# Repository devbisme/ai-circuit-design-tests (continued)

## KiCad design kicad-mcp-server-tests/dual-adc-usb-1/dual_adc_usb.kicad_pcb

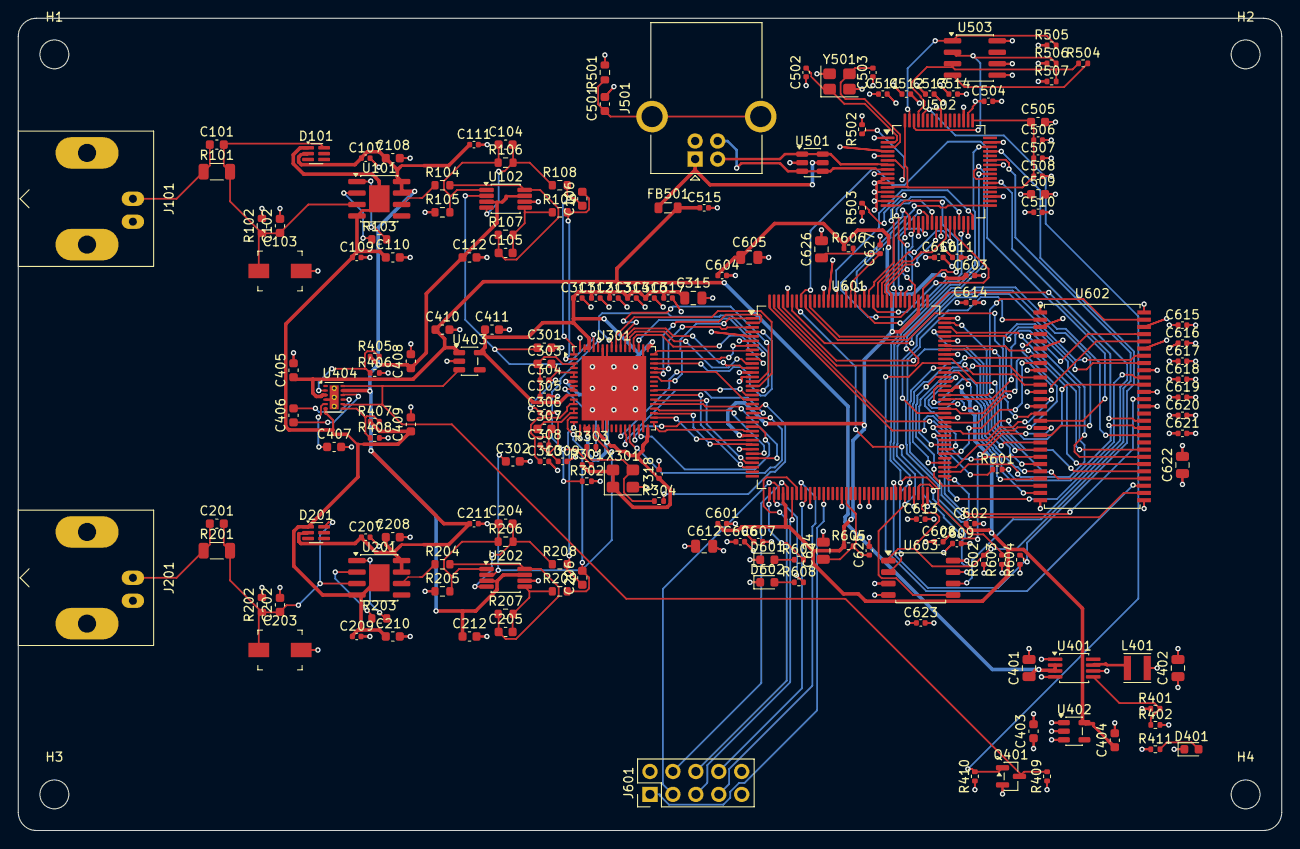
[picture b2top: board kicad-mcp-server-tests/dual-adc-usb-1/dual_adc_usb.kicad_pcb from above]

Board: 4 copper layers, 140.0 x 90.0 mm, 174 parts (0 on the bottom side), 161 nets.

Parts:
C101, C201: 2.2pF C0G; C_0603_1608Metric
C102, C202: 27pF C0G; C_0603_1608Metric
C103, C203: 4.5-20pF; C_Trimmer_Murata_TZB4-A
C104, C105, C204, C205: 22pF C0G; C_0603_1608Metric
C106, C206: 220pF C0G; C_0603_1608Metric
C107, C109, C111, C207, C209, C211, C304, C305, C306, C308, C309, C310, C311, C312, C313, C314, C316, C317, C318, C504, C506, C507, C508, C510, C511, C512, C513, C514, C515, C601, C602, C603, C604, C606, C607, C608, C609, C610, C611, C613, C614, C615, C616, C617, C618, C619, C620, C621, C623, C625, C627: 100nF; C_0402_1005Metric
C108, C110, C112, C208, C210, C212, C403, C404, C406, C410, C411: 1uF; C_0603_1608Metric
C301, C302, C303, C307, C405, C408, C409: 2.2uF; C_0603_1608Metric
C315, C605, C612, C622, C624, C626: 10uF; C_0805_2012Metric
C401: 4.7uF; C_0805_2012Metric
C402: 22uF; C_0805_2012Metric
C407, C505, C509: 4.7uF; C_0603_1608Metric
C501: 4.7nF; C_0603_1608Metric
C502, C503: 18pF; C_0402_1005Metric
D101, D201: BAV199DW; SOT-363_SC-70-6
D401, D601: GREEN; LED_0603_1608Metric
D602: RED; LED_0603_1608Metric
FB501: 600R@100MHz; L_0805_2012Metric
H1, H2, H3, H4: MountingHole_3.2mm_M3
J101, J201: BNC; BNC_Amphenol_B6252HB-NPP3G-50_Horizontal
J501: USB_B; USB_B_OST_USB-B1HSxx_Horizontal
J601: EXP; PinHeader_2x05_P2.54mm_Vertical
L401: 2.2uH; L_Taiyo-Yuden_NR-30xx
Q401: 2N7002; SOT-23
R101, R201: 953k 0.1%; R_1206_3216Metric
R102, R202: 49.9k 0.1%; R_0603_1608Metric
R103, R203: 200; R_0603_1608Metric
R104, R105, R204, R205: 499 0.1%; R_0603_1608Metric
R106, R107, R206, R207: 953 0.1%; R_0603_1608Metric
R108, R109, R208, R209: 49.9; R_0603_1608Metric
R301, R410, R503, R505, R506, R507, R602, R603, R604: 10k; R_0402_1005Metric
R302: 20k; R_0402_1005Metric
R303, R304, R601: 33; R_0402_1005Metric
R401: 316k; R_0402_1005Metric
R402, R409: 100k; R_0402_1005Metric
R405, R407: 115k; R_0402_1005Metric
R406, R408: 49.9k; R_0402_1005Metric
R411, R607, R608: 1k; R_0402_1005Metric
R501: 1M; R_0603_1608Metric
R502: 12k 1%; R_0402_1005Metric
R504: 2.2k; R_0402_1005Metric
R605, R606: 100; R_0402_1005Metric
U101, U201: ADA4817-1ARD; SOIC-8-1EP_3.9x4.9mm_P1.27mm_EP2.29x3mm
U102, U202: THS4521IDGK; VSSOP-8_3x3mm_P0.65mm
U301: LTC2290CUP; QFN-64-1EP_9x9mm_P0.5mm_EP7.15x7.15mm
U401: TPS62160DGK; MSOP-8_3x3mm_P0.65mm
U402: TLV75512PDBV; SOT-23-5
U403: LP5907MFX-3.0; SOT-23-5
U404: LM27762DSSR; WSON-12-1EP_3x2mm_P0.5mm_EP1x2.65_ThermalVias
U501: USBLC6-2SC6; SOT-23-6
U502: FT2232HL; LQFP-64_10x10mm_P0.5mm
U503: 93LC56C; SOIC-8_3.9x4.9mm_P1.27mm
U601: ICE40HX4K-TQ144; TQFP-144_20x20mm_P0.5mm
U602: W9812G6KH-6; TSOP-II-54_22.2x10.16mm_P0.8mm
U603: W25Q32JVSS; SOIC-8_5.3x5.3mm_P1.27mm
X301: SiT8008BI-22-30E-10.000000; Oscillator_SMD_SiT_PQFN-4Pin_3.2x2.5mm
Y501: 12MHz; Crystal_SMD_3225-4Pin_3.2x2.5mm

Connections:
+1V2: C404.1, C601.1, C602.1, C603.1, C604.1, C605.1, R605.1, R606.1, U402.5, U601.27, U601.40, U601.92, U601.111
+3V0: C311.1, C312.1, C313.1, C314.1, C315.1, C316.1, C317.1, C318.1, C411.1, R301.1, U301.7, U301.10, U301.18, U301.19, U301.21, U301.32, U301.49, U301.62, U301.63, U403.5, X301.1, X301.4
+3V3: C402.1, C403.1, C504.1, C509.1, C510.1, C511.1, C512.1, C513.1, C514.1, C606.1, C607.1, C608.1, C609.1, C610.1, C611.1, C612.1, C613.1, C614.1, C615.1, C616.1, C617.1, C618.1, C619.1, C620.1, C621.1, C622.1, C623.1, J601.9, L401.2, R401.1, R409.1, R410.1, R411.1, R503.1, R505.1, R506.1, R507.1, R602.1, R603.1, R604.1, U401.6, U402.1, U402.3, U502.4, U502.9, U502.20, U502.31, U502.42, U502.50, U502.56, U503.6, U503.8, U601.6, U601.30, U601.46, U601.57, U601.72, U601.89, U601.100, U601.108, U601.123, U601.131, U602.1, U602.3, U602.9, U602.14, U602.27, U602.43, U602.49, U603.3, U603.7, U603.8
+4V: C107.1, C108.1, C111.1, C112.1, C207.1, C208.1, C211.1, C212.1, C408.1, D101.2, D201.2, R405.1, U101.7, U101.8, U102.3, U102.7, U201.7, U201.8, U202.3, U202.7, U404.11
+5V: C401.1, C405.1, C410.1, C515.1, FB501.2, U401.2, U401.3, U403.1, U404.3
/ADC/ADC_CLK: R303.2, U301.8, U301.9
/ADC/AINA_N: C106.2, R109.2, U301.2
/ADC/AINA_P: C106.1, R108.2, U301.1
/ADC/AINB_N: C206.2, R209.2, U301.15
/ADC/AINB_P: C206.1, R208.2, U301.16
/ADC/MODE: R301.2, R302.1, U301.60
/ADC/OSC_OUT: R303.1, R304.1, X301.3
/ADC/REFHA: C303.1, C304.1, C305.1, U301.3, U301.4
/ADC/REFHB: C307.1, C308.1, C309.1, U301.13, U301.14
/ADC/REFLA: C303.2, C304.2, C306.1, U301.5, U301.6
/ADC/REFLB: C307.2, C308.2, C310.1, U301.11, U301.12
/ADC/VCMA: C301.1, U102.2, U301.61
/ADC/VCMB: C302.1, U202.2, U301.20
/AFE_A/BUF_FB: R103.2, U101.1
/AFE_A/BUF_INN: R103.1, U101.2
/AFE_A/BUF_OUT: R104.1, U101.6
/AFE_A/DIV: C101.2, C102.1, C103.1, D101.6, R101.2, R102.1, U101.3
/AFE_A/FDA_INN: C104.1, R105.2, R106.1, U102.1
/AFE_A/FDA_INP: C105.1, R104.2, R107.1, U102.8
/AFE_A/FDA_OUTN: C105.2, R107.2, R109.1, U102.5
/AFE_A/FDA_OUTP: C104.2, R106.2, R108.1, U102.4
/AFE_A/IN: C101.1, J101.1, R101.1
/AFE_B/BUF_FB: R203.2, U201.1
/AFE_B/BUF_INN: R203.1, U201.2
/AFE_B/BUF_OUT: R204.1, U201.6
/AFE_B/DIV: C201.2, C202.1, C203.1, D201.6, R201.2, R202.1, U201.3
/AFE_B/FDA_INN: C204.1, R205.2, R206.1, U202.1
/AFE_B/FDA_INP: C205.1, R204.2, R207.1, U202.8
/AFE_B/FDA_OUTN: C205.2, R207.2, R209.1, U202.5
/AFE_B/FDA_OUTP: C204.2, R206.2, R208.1, U202.4
/AFE_B/IN: C201.1, J201.1, R201.1
/FPGA_SDRAM/GPIO0: J601.3, U601.39
/FPGA_SDRAM/GPIO1: J601.4, U601.41
/FPGA_SDRAM/GPIO2: J601.5, U601.42
/FPGA_SDRAM/GPIO3: J601.6, U601.43
/FPGA_SDRAM/GPIO4: J601.7, U601.44
/FPGA_SDRAM/GPIO5: J601.8, U601.45
/FPGA_SDRAM/LED0: R607.2, U601.37
/FPGA_SDRAM/LED0_A: D601.2, R607.1
/FPGA_SDRAM/LED1: R608.2, U601.38
/FPGA_SDRAM/LED1_A: D602.2, R608.1
/FPGA_SDRAM/SD_A0: U601.93, U602.23
/FPGA_SDRAM/SD_A1: U601.94, U602.24
/FPGA_SDRAM/SD_A2: U601.95, U602.25
/FPGA_SDRAM/SD_A3: U601.96, U602.26
/FPGA_SDRAM/SD_A4: U601.97, U602.29
/FPGA_SDRAM/SD_A5: U601.98, U602.30
/FPGA_SDRAM/SD_A6: U601.99, U602.31
/FPGA_SDRAM/SD_A7: U601.101, U602.32
/FPGA_SDRAM/SD_A8: U601.102, U602.33
/FPGA_SDRAM/SD_A9: U601.104, U602.34
/FPGA_SDRAM/SD_A10: U601.105, U602.22
/FPGA_SDRAM/SD_A11: U601.106, U602.35
/FPGA_SDRAM/SD_BA0: U601.107, U602.20
/FPGA_SDRAM/SD_BA1: U601.144, U602.21
/FPGA_SDRAM/SD_CAS_N: U601.138, U602.17
/FPGA_SDRAM/SD_CKE: U601.142, U602.37
/FPGA_SDRAM/SD_CLK: R601.2, U602.38
/FPGA_SDRAM/SD_CLK_SRC: R601.1, U601.143
/FPGA_SDRAM/SD_CS_N: U601.141, U602.19
/FPGA_SDRAM/SD_DQ0: U601.73, U602.2
/FPGA_SDRAM/SD_DQ1: U601.74, U602.4
/FPGA_SDRAM/SD_DQ2: U601.75, U602.5
/FPGA_SDRAM/SD_DQ3: U601.76, U602.7
/FPGA_SDRAM/SD_DQ4: U601.78, U602.8
/FPGA_SDRAM/SD_DQ5: U601.79, U602.10
/FPGA_SDRAM/SD_DQ6: U601.80, U602.11
/FPGA_SDRAM/SD_DQ7: U601.81, U602.13
/FPGA_SDRAM/SD_DQ8: U601.82, U602.42
/FPGA_SDRAM/SD_DQ9: U601.83, U602.44
/FPGA_SDRAM/SD_DQ10: U601.84, U602.45
/FPGA_SDRAM/SD_DQ11: U601.85, U602.47
/FPGA_SDRAM/SD_DQ12: U601.87, U602.48
/FPGA_SDRAM/SD_DQ13: U601.88, U602.50
/FPGA_SDRAM/SD_DQ14: U601.90, U602.51
/FPGA_SDRAM/SD_DQ15: U601.91, U602.53
/FPGA_SDRAM/SD_LDQM: U601.136, U602.15
/FPGA_SDRAM/SD_RAS_N: U601.139, U602.18
/FPGA_SDRAM/SD_UDQM: U601.135, U602.39
/FPGA_SDRAM/SD_WE_N: U601.137, U602.16
/FPGA_SDRAM/TRIG_IN: J601.1, U601.49
/FPGA_SDRAM/VCCPLL0: C624.1, C625.1, R605.2, U601.54
/FPGA_SDRAM/VCCPLL1: C626.1, C627.1, R606.2, U601.126
/Power/AN_EN: Q401.3, R409.2, U403.3, U404.8, U404.12
/Power/CFLY_N: C406.2, U404.9
/Power/CFLY_P: C406.1, U404.10
/Power/CP_NEG: C407.1, U404.5
/Power/FB_3V3: R401.2, R402.1, U401.5
/Power/FB_NEG: R407.2, R408.1, U404.7
/Power/FB_POS: R405.2, R406.1, U404.2
/Power/LED_PWR: D401.2, R411.2
/Power/SW: L401.1, U401.7
/USB/EECLK: R506.2, U502.62, U503.2
/USB/EECS: R505.2, U502.63, U503.1
/USB/EEDATA: R504.1, R507.2, U502.61, U503.3
/USB/EE_DO: R504.2, U503.4
/USB/FT_REF: R502.1, U502.6
/USB/FT_RESET_N: R503.2, U502.14
/USB/OSCI: C502.2, U502.2, Y501.1
/USB/OSCO: C503.2, U502.3, Y501.3
/USB/SHIELD: C501.1, J501.5, R501.1
/USB/USB_DM: J501.2, U501.1, U501.6, U502.7
/USB/USB_DP: J501.3, U501.3, U501.4, U502.8
/USB/V1V8_FT: C505.1, C506.1, C507.1, C508.1, U502.12, U502.37, U502.49, U502.64
/USB/VBUS: FB501.1, J501.1, U501.5
ADC_A0: U301.43, U601.1
ADC_A1: U301.44, U601.2
ADC_A2: U301.45, U601.3
ADC_A3: U301.46, U601.4
ADC_A4: U301.47, U601.7
ADC_A5: U301.48, U601.8
ADC_A6: U301.51, U601.9
ADC_A7: U301.52, U601.10
ADC_A8: U301.53, U601.11
ADC_A9: U301.54, U601.12
ADC_A10: U301.55, U601.15
ADC_A11: U301.56, U601.16
ADC_B0: U301.26, U601.19
ADC_B1: U301.27, U601.22
ADC_B2: U301.28, U601.23
ADC_B3: U301.29, U601.24
ADC_B4: U301.30, U601.25
ADC_B5: U301.33, U601.26
ADC_B6: U301.34, U601.28
ADC_B7: U301.35, U601.29
ADC_B8: U301.36, U601.31
ADC_B9: U301.37, U601.32
ADC_B10: U301.38, U601.33
ADC_B11: U301.39, U601.34
ADC_OFA: U301.57, U601.17
ADC_OFB: U301.40, U601.18
CLK_10M: R304.2, U601.21
FPGA_CDONE: R604.2, U502.45, U601.65
FPGA_CRESET_N: R603.2, U502.46, U601.66
FT_CLK: U502.32, U601.129
FT_D0: U502.16, U601.110
FT_D1: U502.17, U601.112
FT_D2: U502.18, U601.113
FT_D3: U502.19, U601.114
FT_D4: U502.21, U601.115
FT_D5: U502.22, U601.116
FT_D6: U502.23, U601.117
FT_D7: U502.24, U601.118
FT_OE_N: U502.33, U601.125
FT_RD_N: U502.28, U601.121
FT_RXF_N: U502.26, U601.119
FT_SIWU_N: U502.30, U601.124
FT_TXE_N: U502.27, U601.120
FT_WR_N: U502.29, U601.122
GND: C102.2, C103.2, C107.2, C108.2, C109.2, C110.2, C111.2, C112.2, C202.2, C203.2, C207.2, C208.2, C209.2, C210.2, C211.2, C212.2, C301.2, C302.2, C305.2, C306.2, C309.2, C310.2, C311.2, C312.2, C313.2, C314.2, C315.2, C316.2, C317.2, C318.2, C401.2, C402.2, C403.2, C404.2, C405.2, C407.2, C408.2, C409.2, C410.2, C411.2, C501.2, C502.1, C503.1, C504.2, C505.2, C506.2, C507.2, C508.2, C509.2, C510.2, C511.2, C512.2, C513.2, C514.2, C515.2, C601.2, C602.2, C603.2, C604.2, C605.2, C606.2, C607.2, C608.2, C609.2, C610.2, C611.2, C612.2, C613.2, C614.2, C615.2, C616.2, C617.2, C618.2, C619.2, C620.2, C621.2, C622.2, C623.2, C624.2, C625.2, C626.2, C627.2, D401.1, D601.1, D602.1, J101.2, J201.2, J501.4, J601.2, J601.10, Q401.2, R102.2, R105.1, R202.2, R205.1, R302.2, R402.2, R406.2, R408.2, R501.2, R502.2, U102.6, U202.6, U301.17, U301.22, U301.23, U301.31, U301.50, U301.58, U301.59, U301.64, U301.65, U401.1, U401.4, U402.2, U403.2, U404.4, U404.13, U501.2, U502.1, U502.5, U502.10, U502.11, U502.13, U502.15, U502.25, U502.35, U502.47, U502.51, U503.5, U601.5, U601.13, U601.14, U601.53, U601.59, U601.69, U601.86, U601.103, U601.127, U601.132, U601.140, U602.6, U602.12, U602.28, U602.41, U602.46, U602.52, U602.54, U603.4, X301.2, Y501.2, Y501.4
PWREN_N: Q401.1, R410.2, U502.60
SPI_MISO: U502.40, U601.68, U603.2
SPI_MOSI: U502.39, U601.67, U603.5
SPI_SCK: U502.38, U601.70, U603.6
SPI_SS_N: R602.2, U502.43, U601.71, U603.1
VEE: C109.1, C110.1, C209.1, C210.1, C409.1, D101.1, D201.1, R407.1, U101.4, U101.9, U201.4, U201.9, U404.6
